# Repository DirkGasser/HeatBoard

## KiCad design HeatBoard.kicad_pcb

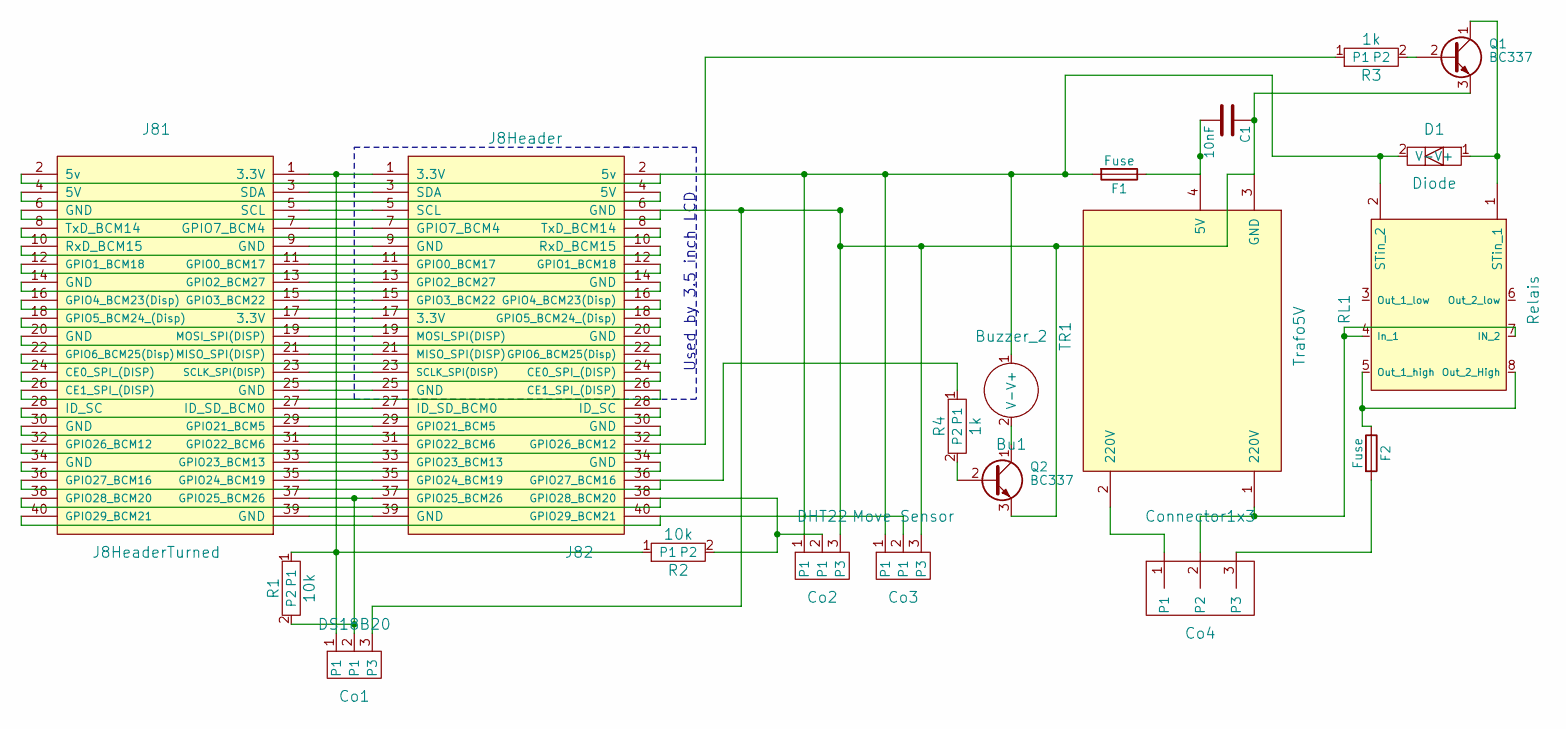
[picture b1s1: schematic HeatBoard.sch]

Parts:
Bu1: Buzzer_2; Buzzer1x2
C1: 10nF; Capacitor_Small
Co1: DS18B20; Conn_Small1x3
Co2: DHT22; Conn_Small1x3
Co3: Move Sensor; Conn_Small1x3
Co4: Connector1x3
D1: Diode
F1, F2: Fuse
J81: J8HeaderTurned; RaspiConnectorTurned
J82: J8Header; RaspiConnector
Q1: BC337
Q2: BC337; TO-92_Molded_Narrow
R1, R2: 10k; Resistor
R3, R4: 1k; Resistor
RL1: Relais
TR1: Trafo5V; Trafo

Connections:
unnamed: Bu1.1 (V+), Co2.1, Co3.1, D1.2 (V-), F1.2, J81.2 (5v), J82.2 (5v), RL1.2 (STin_2)
unnamed: Bu1.2 (V-), Q2.1 (C)
unnamed: C1.1, Co1.3, Co2.3, Co3.3, J81.6 (GND), J82.6 (GND), Q1.3 (E), Q2.3 (E), TR1.3 (GND)
unnamed: C1.2, F1.1, TR1.4 (5V)
unnamed: Co1.1, J81.1 (3.3V), J82.1 (3.3V), R1.1, R2.1
unnamed: Co1.2 (P1), J81.37 (GPIO25_BCM26), J82.37 (GPIO25_BCM26), R1.2
unnamed: Co2.2 (P1), J81.38 (GPIO28_BCM20), J82.38 (GPIO28_BCM20), R2.2
unnamed: Co3.2 (P1), J81.40 (GPIO29_BCM21), J82.40 (GPIO29_BCM21)
unnamed: Co4.1, TR1.2 (220V)
unnamed: Co4.2, RL1.4 (In_1), RL1.7 (IN_2), TR1.1 (220V)
unnamed: Co4.3, F2.2
unnamed: D1.1 (V+), Q1.1 (C), RL1.1 (STin_1)
unnamed: F2.1, RL1.5 (Out_1_high), RL1.8 (Out_2_High)
unnamed: J81.3 (SDA), J82.3 (SDA)
unnamed: J81.4 (5V), J82.4 (5V)
unnamed: J81.5 (SCL), J82.5 (SCL)
unnamed: J81.7 (GPIO7_BCM4), J82.7 (GPIO7_BCM4)
unnamed: J81.8 (TxD_BCM14), J82.8 (TxD_BCM14)
unnamed: J81.9 (GND), J82.9 (GND)
unnamed: J81.10 (RxD_BCM15), J82.10 (RxD_BCM15)
unnamed: J81.11 (GPIO0_BCM17), J82.11 (GPIO0_BCM17)
unnamed: J81.12 (GPIO1_BCM18), J82.12 (GPIO1_BCM18)
unnamed: J81.13 (GPIO2_BCM27), J82.13 (GPIO2_BCM27)
unnamed: J81.14 (GND), J82.14 (GND)
unnamed: J81.15 (GPIO3_BCM22), J82.15 (GPIO3_BCM22)
unnamed: J81.16 (GPIO4_BCM23(Disp)), J82.16 (GPIO4_BCM23(Disp))
unnamed: J81.17 (3.3V), J82.17 (3.3V)
unnamed: J81.18 (GPIO5_BCM24_(Disp)), J82.18 (GPIO5_BCM24_(Disp))
unnamed: J81.19 (MOSI_SPI(DISP)), J82.19 (MOSI_SPI(DISP))
unnamed: J81.20 (GND), J82.20 (GND)
unnamed: J81.21 (MISO_SPI(DISP)), J82.21 (MISO_SPI(DISP))
unnamed: J81.22 (GPIO6_BCM25(Disp)), J82.22 (GPIO6_BCM25(Disp))
unnamed: J81.23 (SCLK_SPI(DISP)), J82.23 (SCLK_SPI(DISP))
unnamed: J81.24 (CE0_SPI_(DISP)), J82.24 (CE0_SPI_(DISP))
unnamed: J81.25 (GND), J82.25 (GND)
unnamed: J81.26 (CE1_SPI_(DISP)), J82.26 (CE1_SPI_(DISP))
unnamed: J81.27 (ID_SD_BCM0), J82.27 (ID_SD_BCM0)
unnamed: J81.28 (ID_SC), J82.28 (ID_SC)
unnamed: J81.29 (GPIO21_BCM5), J82.29 (GPIO21_BCM5)
unnamed: J81.30 (GND), J82.30 (GND)
unnamed: J81.31 (GPIO22_BCM6), J82.31 (GPIO22_BCM6)
unnamed: J81.32 (GPIO26_BCM12), J82.32 (GPIO26_BCM12), R3.1
unnamed: J81.33 (GPIO23_BCM13), J82.33 (GPIO23_BCM13)
unnamed: J81.34 (GND), J82.34 (GND)
unnamed: J81.35 (GPIO24_BCM19), J82.35 (GPIO24_BCM19)
unnamed: J81.36 (GPIO27_BCM16), J82.36 (GPIO27_BCM16), R4.1
unnamed: J81.39 (GND), J82.39 (GND)
unnamed: Q1.2 (B), R3.2
unnamed: Q2.2 (B), R4.2

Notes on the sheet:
Used by 3.5 inch LCD

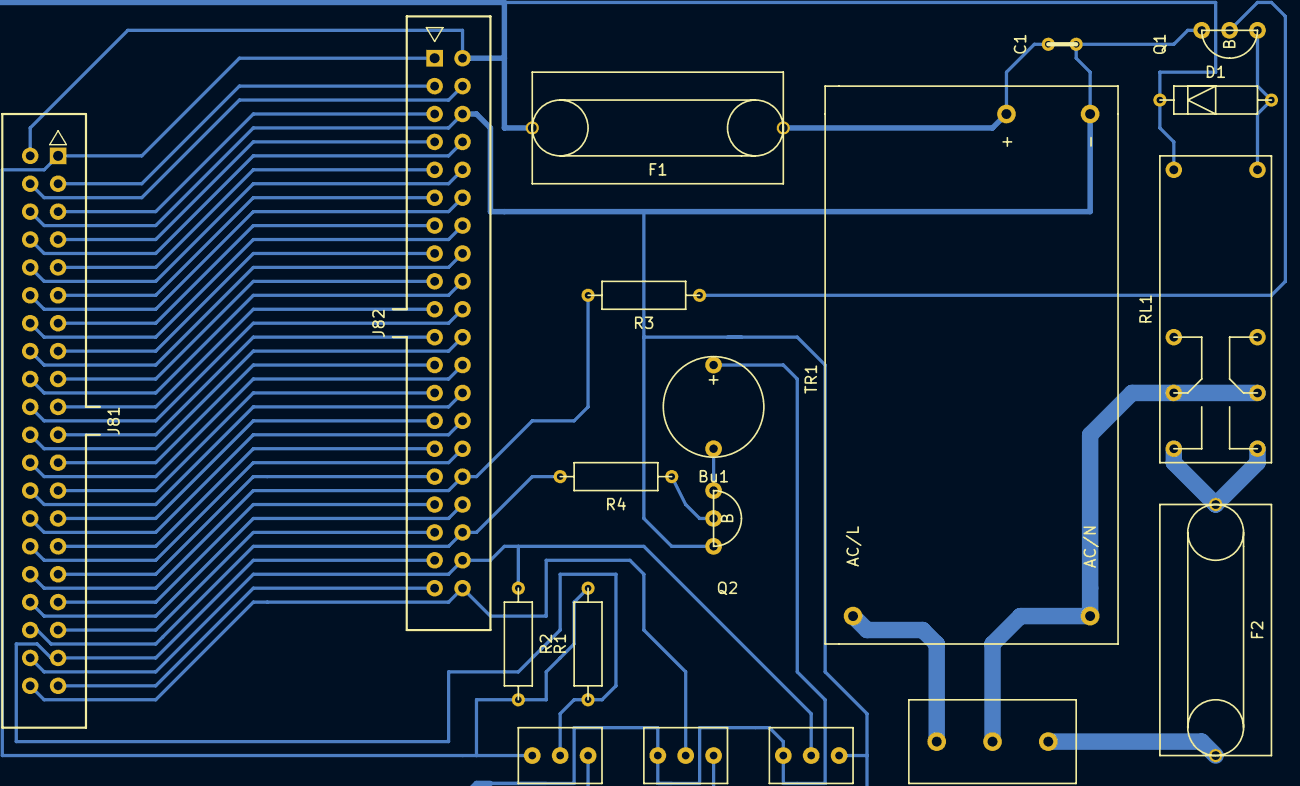
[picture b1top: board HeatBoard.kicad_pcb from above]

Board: 2 copper layers, 19 parts (0 on the bottom side), 49 nets.

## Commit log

2018-11-15 first edition
2018-11-17 First Final
2018-12-18 Raspi Connections move, GND Pin free now
